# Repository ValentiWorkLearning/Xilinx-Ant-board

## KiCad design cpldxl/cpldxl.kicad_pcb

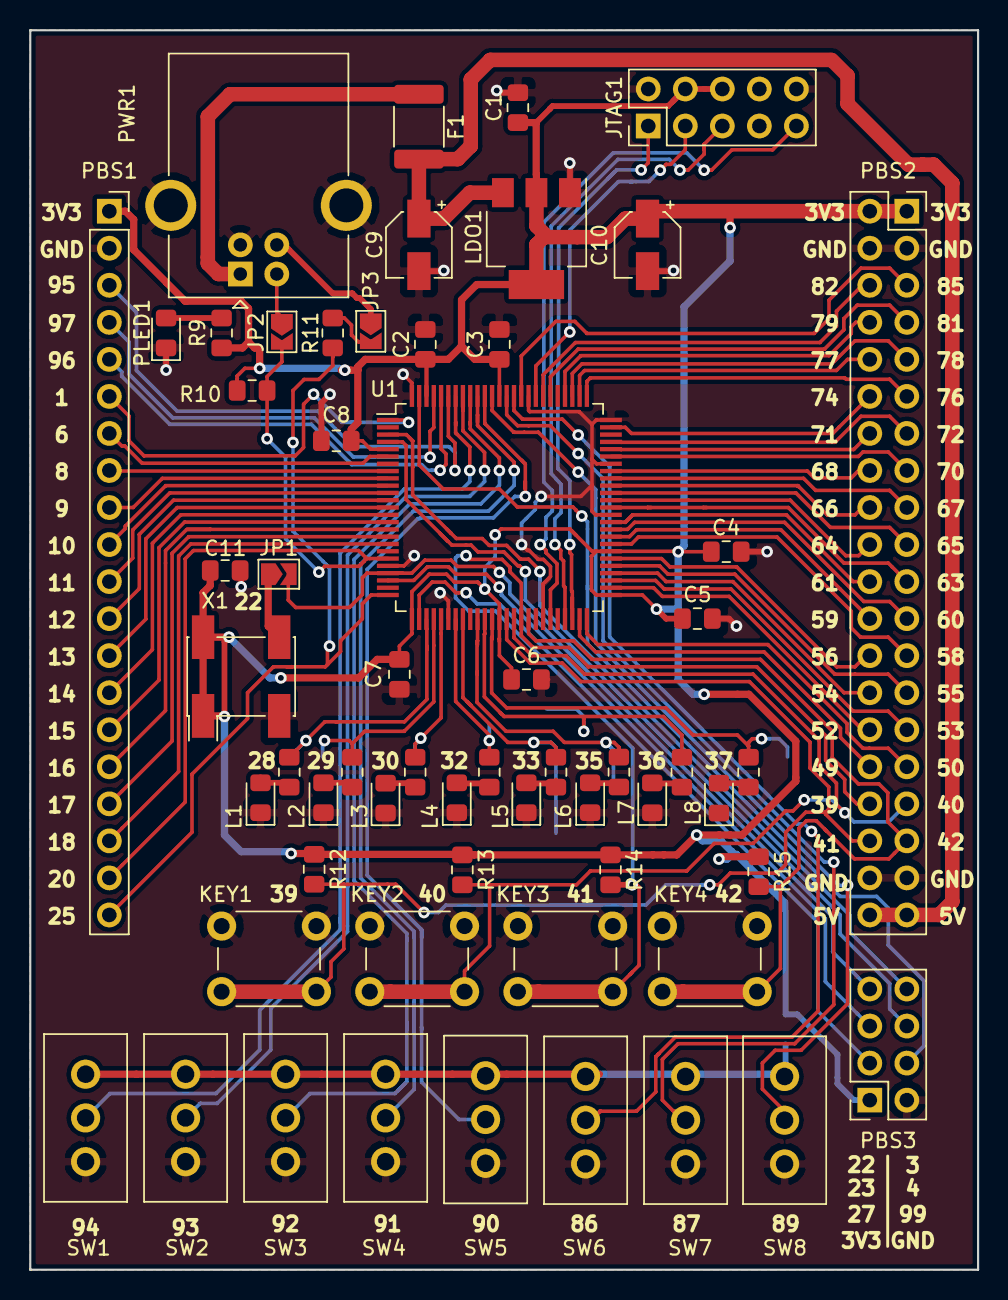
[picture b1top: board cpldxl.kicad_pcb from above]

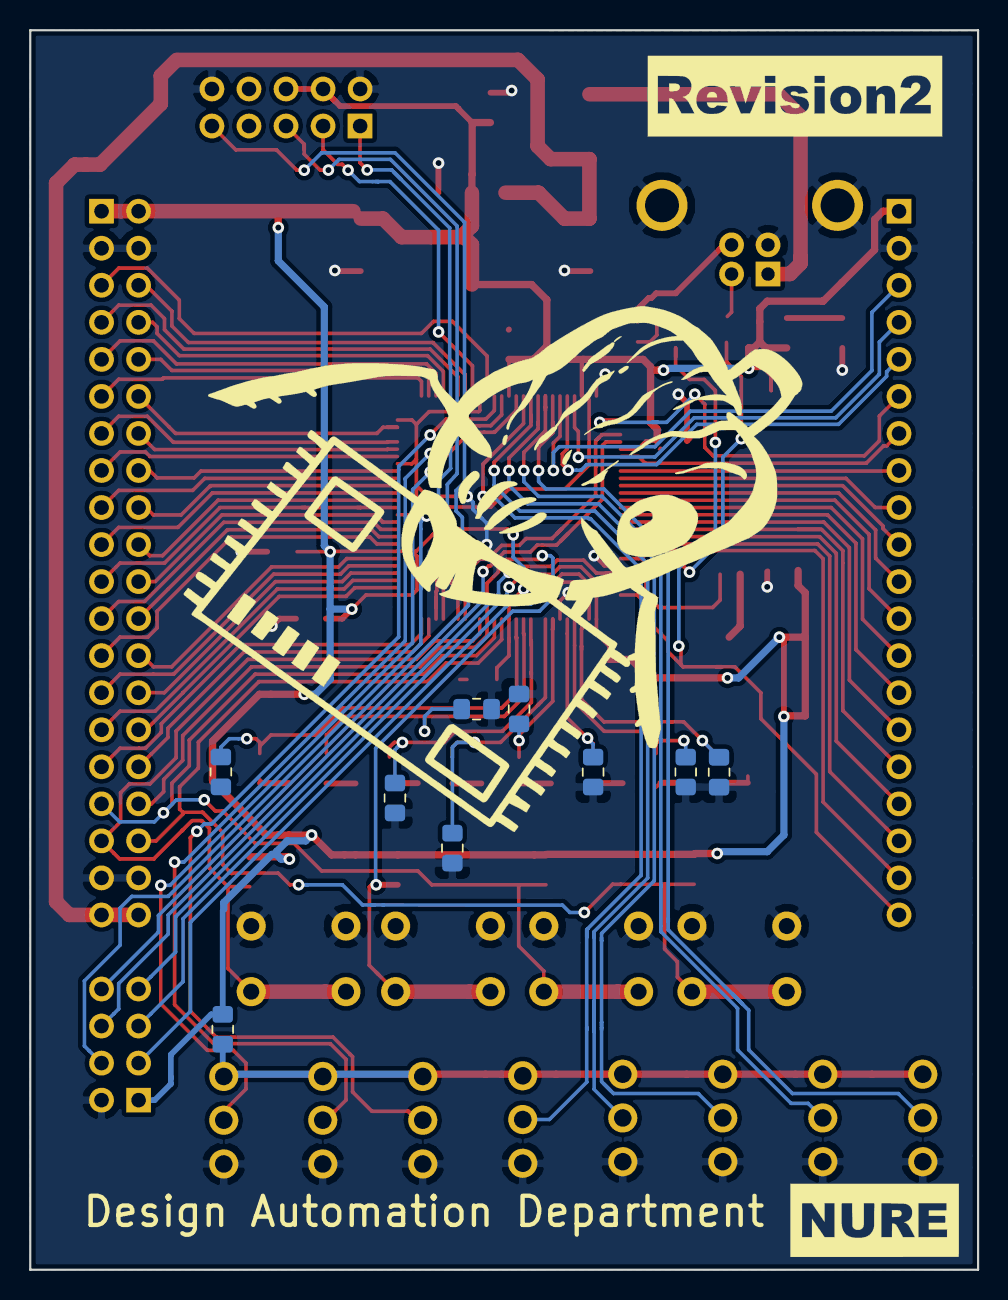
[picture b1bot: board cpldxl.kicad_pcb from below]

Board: 2 copper layers, 65.0 x 85.0 mm, 68 parts (9 on the bottom side), 94 nets.

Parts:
C1, C2, C3, C4, C5, C6, C7, C8, C11: 0.1u; C_0805_2012Metric_Pad1.15x1.40mm_HandSolder
C9, C10: 10u; CP_Elec_4x4.5
F1: Polyfuse_Small; Fuse_1812_4532Metric_Pad1.30x3.40mm_HandSolder
JP1: Jump_OSC; SolderJumper-2_P1.3mm_Open_TrianglePad1.0x1.5mm
JP2: Jump_DN; SolderJumper-2_P1.3mm_Open_TrianglePad1.0x1.5mm
JP3: Jump_DP; SolderJumper-2_P1.3mm_Open_TrianglePad1.0x1.5mm
JTAG1: 10pin; PinHeader_2x05_P2.54mm_Vertical
KEY1, KEY2, KEY3, KEY4: SW_Push; SW_PUSH_6mm
L1, L2, L3, L4, L5, L6, L7, L8: LED; LED_0805_2012Metric_Pad1.15x1.40mm_HandSolder
LDO1: LM1117-3.3; SOT-223-3_TabPin2
PBS1: Conn_PBS1x25; PinSocket_1x20_P2.54mm_Vertical
PBS2: Conn_PBS2x20; PinSocket_2x20_P2.54mm_Vertical
PBS3: Conn_PBS2x4; PinSocket_2x04_P2.54mm_Vertical
PLED1: LED; LED_0805_2012Metric_Pad1.15x1.40mm_HandSolder
PWR1: USB_BF; USB_B_OST_USB-B1HSxx_Horizontal
R1, R2, R3, R4, R5, R6, R7, R8: R; R_0805_2012Metric_Pad1.15x1.40mm_HandSolder
R9, R11: 82; R_0805_2012Metric_Pad1.15x1.40mm_HandSolder
R10, R12, R13, R14, R15, R16, R17, R18, R19, R20, R21, R22, R23, R24: 2k; R_0805_2012Metric_Pad1.15x1.40mm_HandSolder
SW1, SW2, SW3, SW4, SW5, SW6, SW7, SW8: SW_SPDT; SW_SPDT_SS12N12E (2)
U1: XC9572XL-TQ100; TQFP-100_14x14mm_P0.5mm
X1: KX-200; Oscillator_SMD_Fordahl_DFAS11-4Pin_7.0x5.0mm_HandSoldering

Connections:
+3V3: C1.1, C2.1, C3.1, C4.1, C5.1, C6.1, C7.1, C8.1, C10.1, C11.1, JTAG1.4, JTAG1.6, LDO1.2, PBS1.1, PBS2.1, PBS2.2, PBS3.1, R9.1, R10.1, R12.1, R13.1, R14.1, R15.1, R16.1, U1.5, U1.26, U1.38, U1.51, U1.57, U1.88, U1.98, X1.1, X1.4
/BANK1_1: PBS1.16, U1.16
/BANK1_2: PBS1.13, U1.13
/BANK1_3: PBS1.18, U1.18
/BANK1_4: JP2.2, PBS1.19, R10.2, U1.20
/BANK1_5: PBS1.14, U1.14
/BANK1_6: PBS1.15, U1.15
/BANK1_7: PBS1.20, R11.2, U1.25
/BANK1_8: PBS1.17, U1.17
/BANK1_10: R1.1, R17.1, U1.28
/BANK1_12: R5.1, R21.1, U1.33
/BANK1_13: R7.1, R23.1, U1.36
/BANK1_15: R2.1, R18.1, U1.29
/BANK1_16: KEY1.2, PBS2.36, R12.2, U1.39
/BANK1_17: R3.1, R19.1, U1.30
/BANK1_18: KEY2.2, PBS2.33, R13.2, U1.40
/BANK1_GCK1: JP1.2, PBS3.7, U1.22
/BANK1_GCK2: PBS3.5, U1.23
/BANK1_GCK3: PBS3.3, U1.27
/BANK2_1: SW7.2, U1.87
/BANK2_2: SW1.2, U1.94
/BANK2_3: SW4.2, U1.91
/BANK2_4: SW2.2, U1.93
/BANK2_5: PBS1.3, U1.95
/BANK2_6: PBS1.5, U1.96
/BANK2_8: PBS1.4, U1.97
/BANK2_10: PBS1.6, U1.1
/BANK2_12: PBS1.7, U1.6
/BANK2_13: PBS1.8, U1.8
/BANK2_14: PBS1.9, U1.9
/BANK2_15: PBS1.11, U1.11
/BANK2_16: PBS1.10, U1.10
/BANK2_17: PBS1.12, U1.12
/BANK2_18: SW3.2, U1.92
/BANK2_GSR: PBS3.4, U1.99
/BANK2_GTS1: PBS3.8, U1.3
/BANK2_GTS2: PBS3.6, U1.4
/BANK3_1: KEY3.2, PBS2.34, R14.2, U1.41
/BANK3_2: R4.1, R20.1, U1.32
/BANK3_3: PBS2.32, U1.49
/BANK3_4: PBS2.31, U1.50
/BANK3_5: R6.1, R22.1, U1.35
/BANK3_6: PBS2.29, U1.53
/BANK3_7: PBS2.28, U1.54
/BANK3_8: R8.1, R24.1, U1.37
/BANK3_9: KEY4.2, PBS2.35, R15.2, U1.42
/BANK3_10: PBS2.23, U1.60
/BANK3_11: PBS2.30, U1.52
/BANK3_12: PBS2.22, U1.61
/BANK3_13: PBS2.21, U1.63
/BANK3_14: PBS2.27, U1.55
/BANK3_15: PBS2.26, U1.56
/BANK3_16: PBS2.20, U1.64
/BANK3_17: PBS2.25, U1.58
/BANK3_18: PBS2.24, U1.59
/BANK4_1: PBS2.19, U1.65
/BANK4_2: PBS2.17, U1.67
/BANK4_3: PBS2.14, U1.71
/BANK4_4: PBS2.13, U1.72
/BANK4_5: PBS2.16, U1.68
/BANK4_6: PBS2.11, U1.76
/BANK4_7: PBS2.10, U1.77
/BANK4_8: PBS2.15, U1.70
/BANK4_9: PBS2.18, U1.66
/BANK4_10: PBS2.7, U1.81
/BANK4_11: PBS2.12, U1.74
/BANK4_12: PBS2.6, U1.82
/BANK4_13: PBS2.5, U1.85
/BANK4_14: PBS2.9, U1.78
/BANK4_15: SW8.2, U1.89
/BANK4_16: SW6.2, U1.86
/BANK4_17: SW5.2, U1.90
/BANK4_18: PBS2.8, U1.79
/JTAG_TCK: JTAG1.1, U1.48
/JTAG_TDI: JTAG1.9, U1.45
/JTAG_TDO: JTAG1.3, U1.83
/JTAG_TMS: JTAG1.5, U1.47
/OSC: JP1.1, X1.3
/USB_5V: C9.1, F1.1, LDO1.3, PBS2.39, PBS2.40
GND: C1.2, C2.2, C3.2, C4.2, C5.2, C6.2, C7.2, C8.2, C9.2, C10.2, C11.2, JTAG1.2, JTAG1.10, KEY1.1, KEY2.1, KEY3.1, KEY4.1, L1.1, L2.1, L3.1, L4.1, L5.1, L6.1, L7.1, L8.1, LDO1.1, PBS1.2, PBS2.3, PBS2.4, PBS2.37, PBS2.38, PBS3.2, PLED1.1, PWR1.4, PWR1.5, R17.2, R18.2, R19.2, R20.2, R21.2, R22.2, R23.2, R24.2, SW1.3, SW2.3, SW3.3, SW4.3, SW5.3, SW6.3, SW7.3, SW8.3, U1.21, U1.31, U1.44, U1.62, U1.69, U1.75, U1.84, U1.100, X1.2
unnamed: F1.2, PWR1.1
unnamed: JP2.1, PWR1.2
unnamed: JP3.1, PWR1.3
unnamed: JP3.2, R11.1
unnamed: L1.2, R1.2
unnamed: L2.2, R2.2
unnamed: L3.2, R3.2
unnamed: L4.2, R4.2
unnamed: L5.2, R5.2
unnamed: L6.2, R6.2
unnamed: L7.2, R7.2
unnamed: L8.2, R8.2
unnamed: PLED1.2, R9.2
unnamed: R16.2, SW1.1, SW2.1, SW3.1, SW4.1, SW5.1, SW6.1, SW7.1, SW8.1

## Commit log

2019-06-23 Updated schematic
2019-06-25 Fixed bank 1.18 vias position
2019-09-13 Added board description
